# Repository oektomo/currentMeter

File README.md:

Inverter and Battery project

menggunakan bluepill

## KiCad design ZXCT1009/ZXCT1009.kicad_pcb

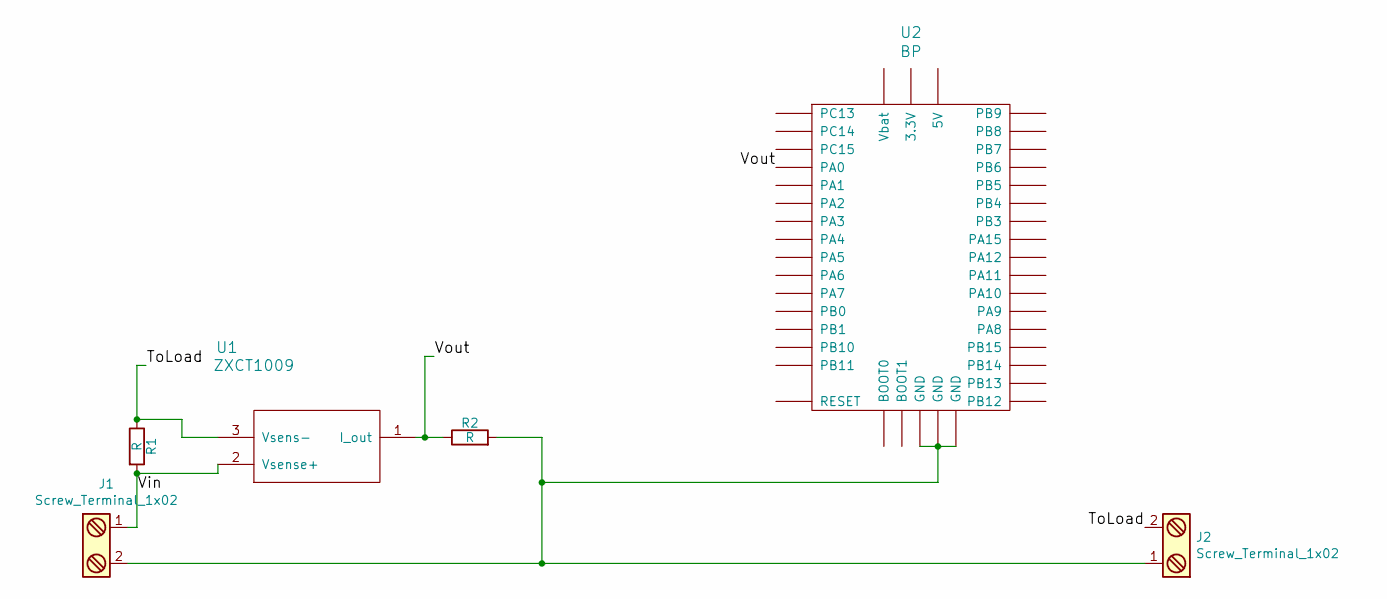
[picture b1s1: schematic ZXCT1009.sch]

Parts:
J1, J2: Screw_Terminal_1x02; TerminalBlock_Pheonix_MKDS1.5-2pol
R1: R; R_0805_HandSoldering
R2: R; Resistor_Horizontal_RM20mm
U1: ZXCT1009; SOT-23
U2: BP; DIP-40__600_ELL

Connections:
/ToLoad: J2.2, R1.1, U1.3 (Vsens-)
/Vout: R2.1, U1.1 (I_out), U2.25 (PA0)
unnamed: J1.1, R1.2, U1.2 (Vsense+)
unnamed: J1.2, J2.1, R2.2, U2.19 (GND), U2.39 (GND), U2.40 (GND)

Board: 2 copper layers, 6 parts (0 on the bottom side), 4 nets, no tracks yet.

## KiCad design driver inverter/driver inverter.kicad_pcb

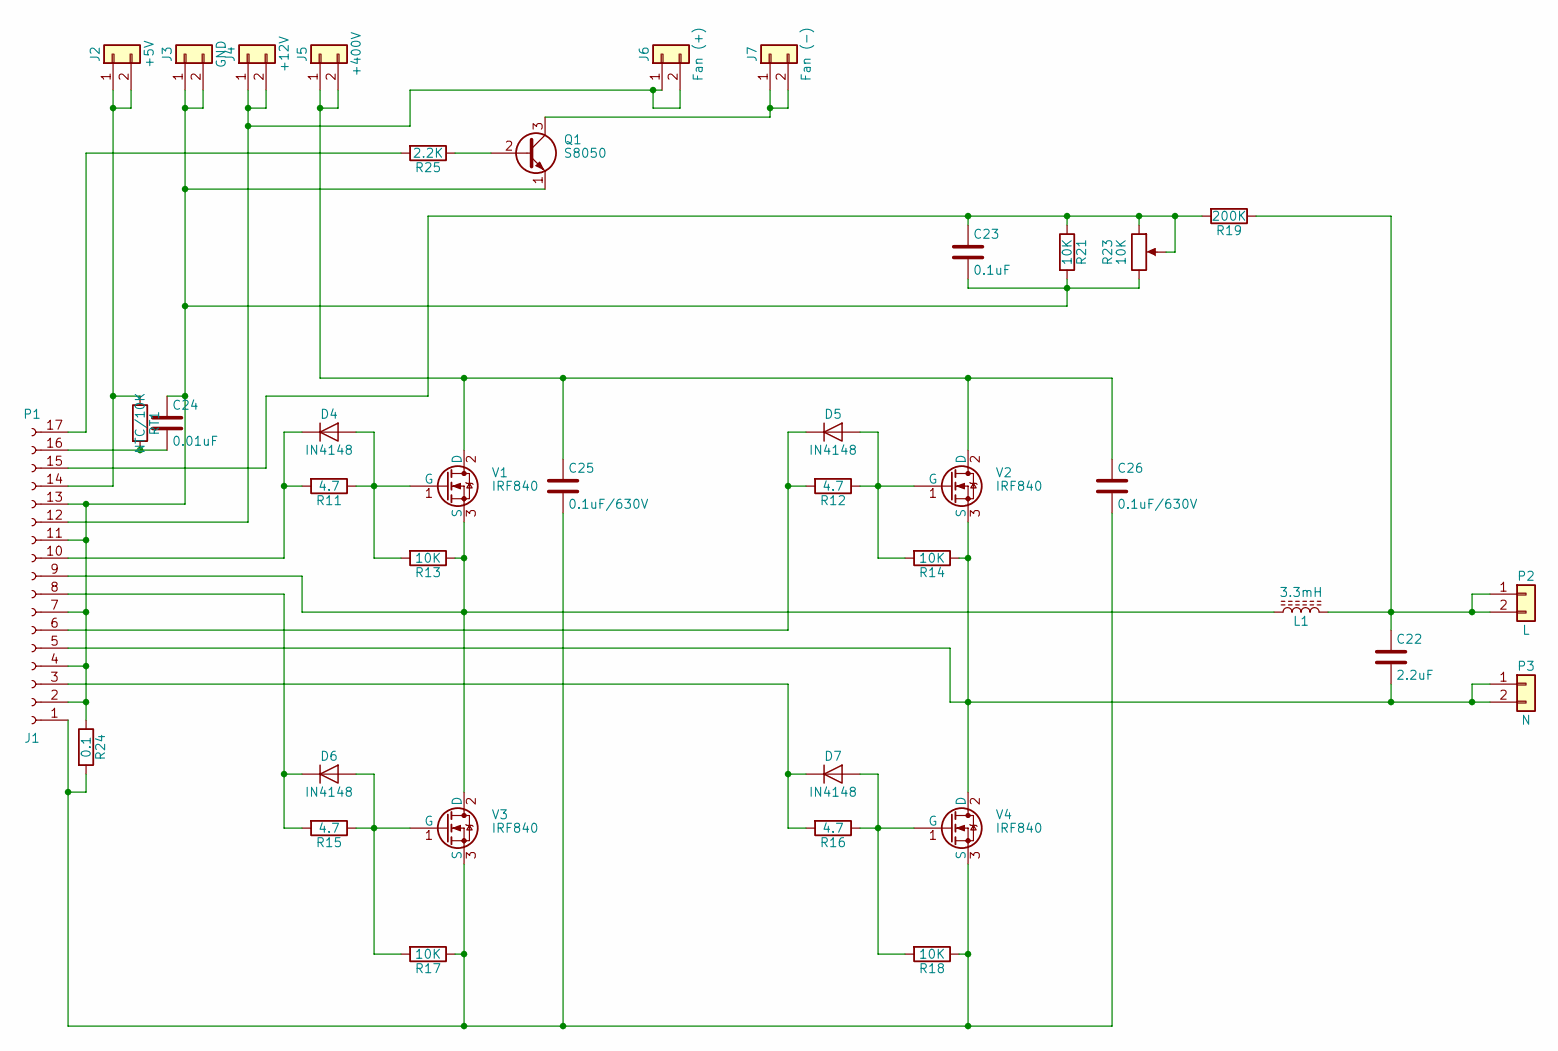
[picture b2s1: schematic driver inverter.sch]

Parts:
C22: 2.2uF; CP_Radial_Tantal_D4.5mm_P2.50mm
C23: 0.1uF; CP_Radial_Tantal_D4.5mm_P2.50mm
C24: 0.01uF; CP_Radial_Tantal_D4.5mm_P2.50mm
C25, C26: 0.1uF/630V; CP_Radial_Tantal_D4.5mm_P2.50mm
D4, D5, D6, D7: IN4148; D_T-1_P10.16mm_Horizontal
J1: P1; Pin_Header_Straight_1x17_Pitch2.54mm
J2: +5V; Pin_Header_Straight_1x02_Pitch2.54mm
J3: GND; Pin_Header_Straight_1x02_Pitch2.54mm
J4: +12V; Pin_Header_Straight_1x02_Pitch2.54mm
J5: +400V; Pin_Header_Straight_1x02_Pitch2.54mm
J6: Fan (+); Pin_Header_Straight_1x02_Pitch2.54mm
J7: Fan (-); Pin_Header_Straight_1x02_Pitch2.54mm
L1: 3.3mH; L_Toroid_Horizontal_D40.0mm_P48.26mm
P2: L; Pin_Header_Straight_1x02_Pitch2.54mm
P3: N; Pin_Header_Straight_1x02_Pitch2.54mm
Q1: S8050; TO-92_Molded_Narrow
R11, R12, R15, R16: 4.7; R_Axial_DIN0411_L9.9mm_D3.6mm_P15.24mm_Horizontal
R13, R14, R17, R18, R21: 10K; R_Axial_DIN0411_L9.9mm_D3.6mm_P15.24mm_Horizontal
R19: 200K; R_Axial_DIN0411_L9.9mm_D3.6mm_P15.24mm_Horizontal
R23: 10K; Potentiometer_Trimmer_VishaySpectrol_Econtrim-Type36M
R24: 0.1; R_Axial_DIN0411_L9.9mm_D3.6mm_P15.24mm_Horizontal
R25: 2.2K; R_Axial_DIN0411_L9.9mm_D3.6mm_P15.24mm_Horizontal
RT1: NTC/10K; R_Axial_DIN0411_L9.9mm_D3.6mm_P15.24mm_Horizontal
V1, V2, V3, V4: IRF840; TO-220_Vertical

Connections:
unnamed: C22.1, L1.2, P2.1, P2.2, R19.1
unnamed: C22.2, J1.5, P3.1, P3.2, R14.1, V2.3 (S), V4.2 (D)
unnamed: C23.1, J1.15, R19.2, R21.1, R23.1, R23.2
unnamed: C23.2, C24.1, J1.2, J1.4, J1.7, J1.11, J1.13, J3.1, J3.2, Q1.1 (E), R21.2, R23.3, R24.1
unnamed: C24.2, J1.16, RT1.2
unnamed: C25.1, C26.1, J5.1, J5.2, V1.2 (D), V2.2 (D)
unnamed: C25.2, C26.2, J1.1, R17.1, R18.1, R24.2, V3.3 (S), V4.3 (S)
unnamed: D4.1 (K), J1.10, R11.2
unnamed: D4.2 (A), R11.1, R13.2, V1.1 (G)
unnamed: D5.1 (K), J1.6, R12.2
unnamed: D5.2 (A), R12.1, R14.2, V2.1 (G)
unnamed: D6.1 (K), J1.8, R15.2
unnamed: D6.2 (A), R15.1, R17.2, V3.1 (G)
unnamed: D7.1 (K), J1.3, R16.2
unnamed: D7.2 (A), R16.1, R18.2, V4.1 (G)
unnamed: J1.9, L1.1, R13.1, V1.3 (S), V3.2 (D)
unnamed: J1.12, J4.1, J4.2, J6.1, J6.2
unnamed: J1.14, J2.1, J2.2, RT1.1
unnamed: J1.17, R25.2
unnamed: J7.1, J7.2, Q1.3 (C)
unnamed: Q1.2 (B), R25.1

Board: 2 copper layers, 38 parts (0 on the bottom side), 21 nets, no tracks yet.

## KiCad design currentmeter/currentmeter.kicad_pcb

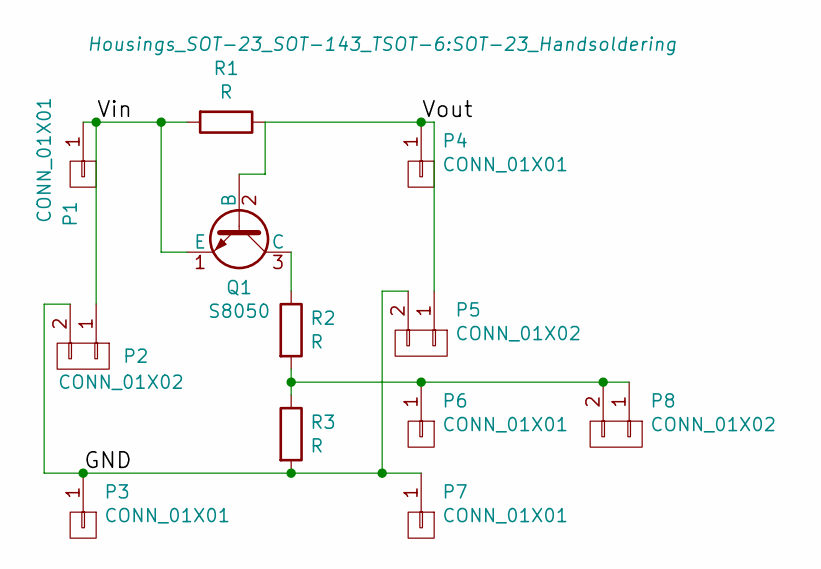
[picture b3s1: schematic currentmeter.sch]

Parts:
P1, P3, P4, P6, P7: CONN_01X01; 1pin
P2, P5, P8: CONN_01X02; Pin_Header_Straight_1x02_Pitch3.96mm_Friction_Lock
Q1: S8050; SOT-23_Handsoldering
R1, R2, R3: R; R3-LARGE_PADS

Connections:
/GND: P2.2, P3.1, P5.2, P7.1, R3.2
/Vin: P1.1, P2.1, Q1.1 (E), R1.2
/Vout: P4.1, P5.1, Q1.2 (B), R1.1
unnamed: P6.1, P8.1, P8.2, R2.2, R3.1
unnamed: Q1.3 (C), R2.1

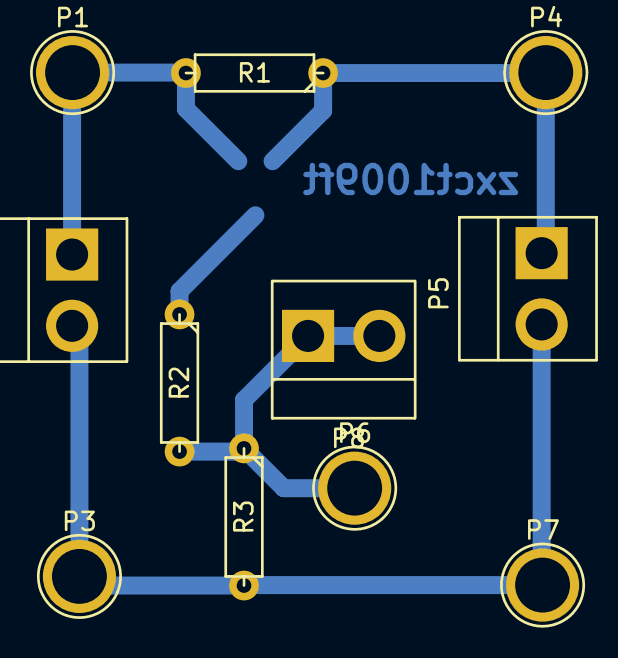
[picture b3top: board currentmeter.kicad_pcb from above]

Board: 2 copper layers, 12 parts (1 on the bottom side), 5 nets.

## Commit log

2017-09-18 initial init dari Felix
2017-09-18 adding bluepill.lib
2017-09-18 buat PCB, ternyata bluepill.lib tidak sesuai penomoran kakinya, felix perbaiki
2017-09-18 adding personal current meter project
2017-09-18 nambahin driver inverter
2017-09-27 adding terminal
2017-09-27 adding readme file
2017-10-17 nambahkan header untuk UART dan pin lain
2017-10-17 perbaharui README.md
2017-10-31 adding octave-script to calculate Rsense and Rout
2017-11-01 adding serial Desktop soft, still can't compile
2017-11-01 correcting compile problem, serial untested
2017-11-02 done reading from serial and write to file
2017-11-02 correcting user manual
